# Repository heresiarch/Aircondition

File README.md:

# Aircondition
A Project using TX21IT+ wireless 868Mhz sensors with RFM12 and PIC24F to control air ventilators based on absolute humidity.
You will find the whole C source and Eagle project files inside.
The Circuit and Software uses the following technologies:
* OW protocoll managing config data for DS2430A 1 wire 256 EEPROM
* Microchip MCU PIC24F P24FJ32GB002
* Hope RFM12B IRQ driven communication with TX21IT+ LaCrosse IT+ Weather sensors
* IC2 communication with Newhaven LCD Display NHD-C0216CiZ-FN-FBW-3V (which was tricky)
* Rotary encoder using digital filter algorithm for debouncing for configuring the system  

The setup is very simple:  
0. The system checks for valid config and CRC in the EEPROM and if OK goes to 3 or step 1  
1. You have to register the 2 TX21IT+ sensors each time you change their battery the get a new ID.  
2. Then you setup in sensor, out sensor, absolute humidity threshold, pause time, run time for ventitalors which is stored in the OW EEPROM  
3. Then the mainloop starts  
3.1. In the Mainlopp the MCU will listen with the RFM12B for 30 TX21IT+ records  
3.2. The ID of the records is used to match in and out sensors configured in step 1 and 2, if no sensor matches found it starts @1   
3.3 The temperature and relative humidity will be used to calculate absolute humidity for the in and out sensor  
3.5 If abs-hum-in > (threshold + abs-hum-out) the AC ventilators will be switched with an SCR  will run as long the configured runtime in step 2  
3.6. The system waits until the pause time is over and starte @3  
At any time a long press on the rotary knob will start reconfiguring mode step 1  

The system runs rockstable since 10 years in my garage with Marley Silenzio Ventilators.  
Not shown is the snubber circuit using a TVS, X2 capacitor and an high voltage resistor to reduce spikes to protect the SCR.
Bottom ventilator blows air from outside, top ventilator blows air to outside.
No moldy smell and always uses the right time for air condition to prevent mold creation during all seasons.  
The project uses MPLABX and has also a .project Eclipse file which I used to utilize Git Eclipse integration to manage versioning.

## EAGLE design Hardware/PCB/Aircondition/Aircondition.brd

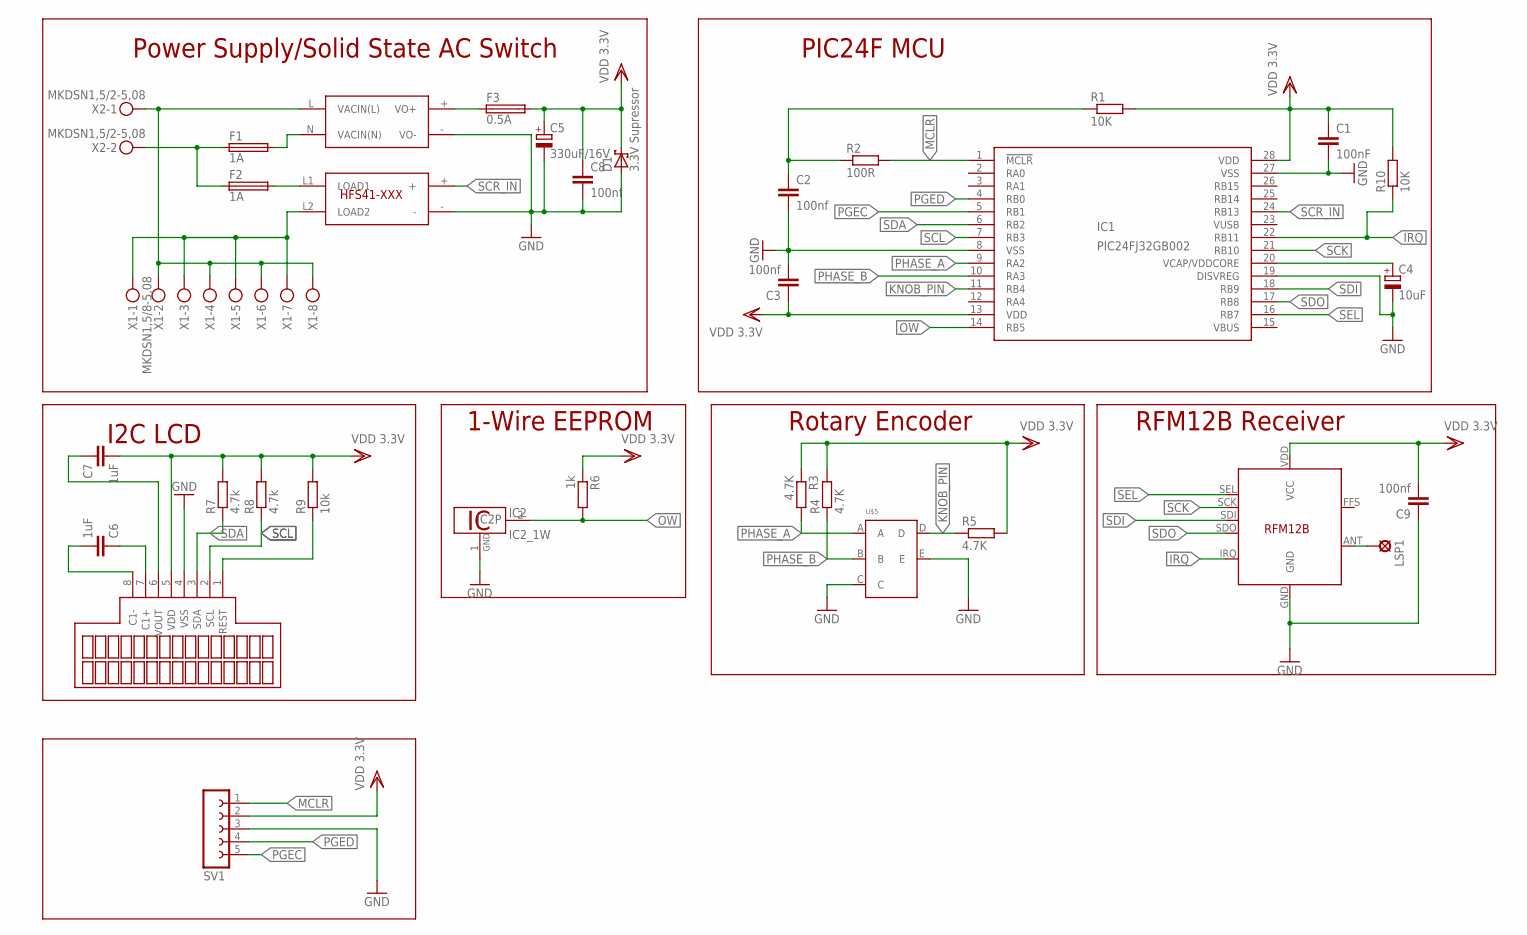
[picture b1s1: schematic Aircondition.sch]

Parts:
C1: 100nF; C025-025X050
C2, C8: 100nf; C025-025X050
C3, C9: 100nf; C102-043X133
C4: 10uF; E5-5
C5: 330uF/16V; E5-10,5
C6, C7: 1uF; C025-025X050
D1: 3.3V Supressor; C4111-15
F1, F2: 1A; SH22,5A
F3: 0.5A; SH22,5A
IC1: PIC24FJ32GB002; DIL28-3
IC2: DS2431; TO92-
LSP1: ANT; LSP10
R1: 10K; 0204/5
R2: 100R; 0204/5
R3, R4, R5: 4.7K; 0204/7
R6: 1k; 0207/2V
R7, R8: 4.7k; 0204/5
R9: 10k; 0204/5
R10: 10K; 0207/10
SV1: FE05-1
U$1: RAC01-3.3SC; RAC01-XXSC
U$2: HFS41D-240A5Z-NGSTANDARD; HFS41-EXPOXY-RESIN
U$3: NHD-C0216CIZ-FN-FBW-3VSIL8-2.54; SIL8-2.54
U$4: RFM12B
U$5: ENCODER-E; ENCODER
X1: MKDSN1,5/8-5,08
X2: MKDSN1,5/2-5,08

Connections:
GND: C1.2, C2.2, C3.2, C4.-, C5.-, C8.2, C9.1, D1.A, IC1.8 (VSS), IC1.19 (DISVREG), IC1.27 (VSS), IC2.1 (GND), SV1.3, U$1.- (VO-), U$2.-, U$3.4 (VSS), U$4.GND, U$5.C, U$5.E
IRQ: IC1.22 (RB11), R10.1, U$4.IRQ
KNOB_PIN: IC1.11 (RB4), R5.1, U$5.D
MCLR: IC1.1 (!MCLR), R2.2, SV1.1
unnamed: F1.2, U$1.N (VACIN(N))
unnamed: F2.2, U$2.L1 (LOAD1)
unnamed: F1.1, F2.1, X2.2
unnamed: U$2.L2 (LOAD2), X1.1, X1.3, X1.5, X1.7
unnamed: C2.1, R1.1, R2.1
unnamed: U$1.L (VACIN(L)), X1.2, X1.4, X1.6, X1.8, X2.1
unnamed: F3.1, U$1.+ (VO+)
unnamed: C4.+, IC1.20 (VCAP/VDDCORE)
unnamed: LSP1.MP, U$4.ANT
unnamed: C6.2, U$3.8 (C1-)
unnamed: C6.1, U$3.7 (C1+)
unnamed: C7.1, U$3.6 (VOUT)
unnamed: R9.1, U$3.1 (REST)
OW: IC1.14 (RB5), IC2.2 (1W), R6.2
PGEC: IC1.5 (RB1), SV1.5
PGED: IC1.4 (RB0), SV1.4
PHASE_A: IC1.9 (RA2), R3.2, U$5.A
PHASE_B: IC1.10 (RA3), R4.1, U$5.B
SCK: IC1.21 (RB10), U$4.SCK
SCL: IC1.7 (RB3), R8.1, U$3.2 (SCL)
SCR_IN: IC1.24 (RB13), U$2.+
SDA: IC1.6 (RB2), R7.1, U$3.3 (SDA)
SDI: IC1.18 (RB9), U$4.SDI
SDO: IC1.17 (RB8), U$4.SDO
SEL: IC1.16 (RB7), U$4.SEL
VDD: C1.1, C3.1, C5.+, C7.2, C8.1, C9.2, D1.C, F3.2, IC1.13 (VDD), IC1.28 (VDD), R1.2, R3.1, R4.2, R5.2, R6.1, R7.2, R8.2, R9.2, R10.2, SV1.2, U$3.5 (VDD), U$4.VDD (VCC)

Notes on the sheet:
Power Supply/Solid State AC Switch
I2C LCD
1-Wire EEPROM
Rotary Encoder
PIC24F MCU
RFM12B Receiver

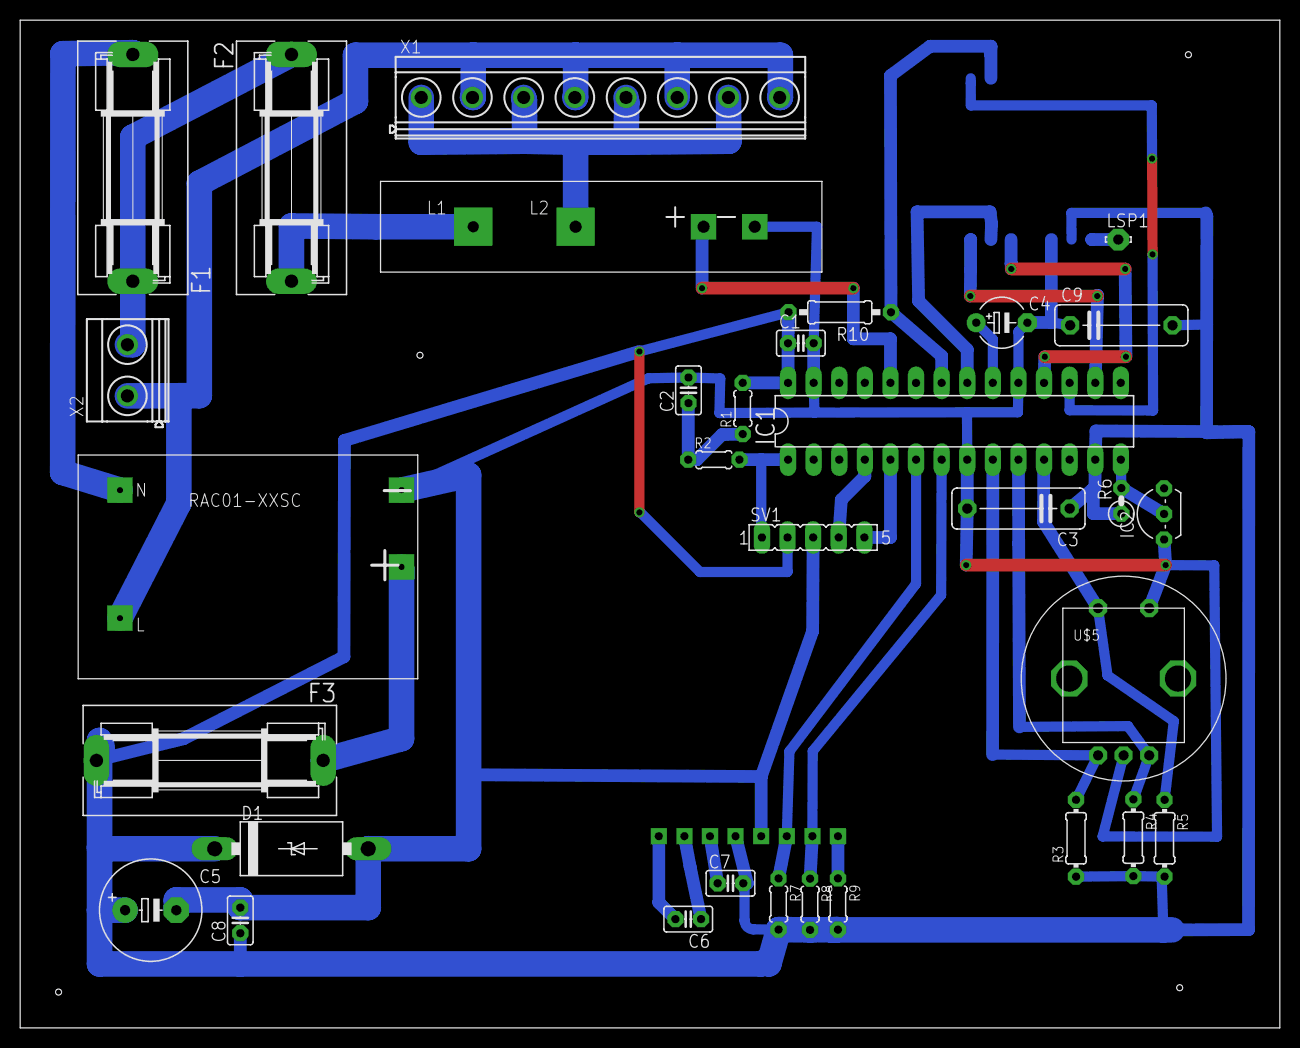
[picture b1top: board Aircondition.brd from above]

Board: 2 copper layers, 125.0 x 100.0 mm, 34 parts (1 on the bottom side), 30 nets.

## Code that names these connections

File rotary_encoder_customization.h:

/* 
 * File:   rotary_encoder_customization.h
 * Author: rene
 *
 * Created on 24. Mai 2014, 09:57
 */

#ifndef ROTARY_ENCODER_CUSTOMIZATION_H
#define	ROTARY_ENCODER_CUSTOMIZATION_H
#include <xc.h>
#define FCY 8000000UL
#include <libpic30.h>
//Rotary Encoder PIN Definitions
#define PHASE_B  PORTAbits.RA2
#define PHASE_A  PORTAbits.RA3
#define KNOB_PIN PORTBbits.RB4

#endif	/* ROTARY_ENCODER_CUSTOMIZATION_H */

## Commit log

2015-02-06 initial
2015-02-06 new commit
2015-02-06 push new project structure
2015-02-06 markdown
2015-02-06 untrack
2015-02-06 untrack 2
2015-02-06 untrack 3
2015-02-06 changed layout md
2015-02-06 teschts
2015-02-06 test with ssh
2015-04-19 added break time config after runs
